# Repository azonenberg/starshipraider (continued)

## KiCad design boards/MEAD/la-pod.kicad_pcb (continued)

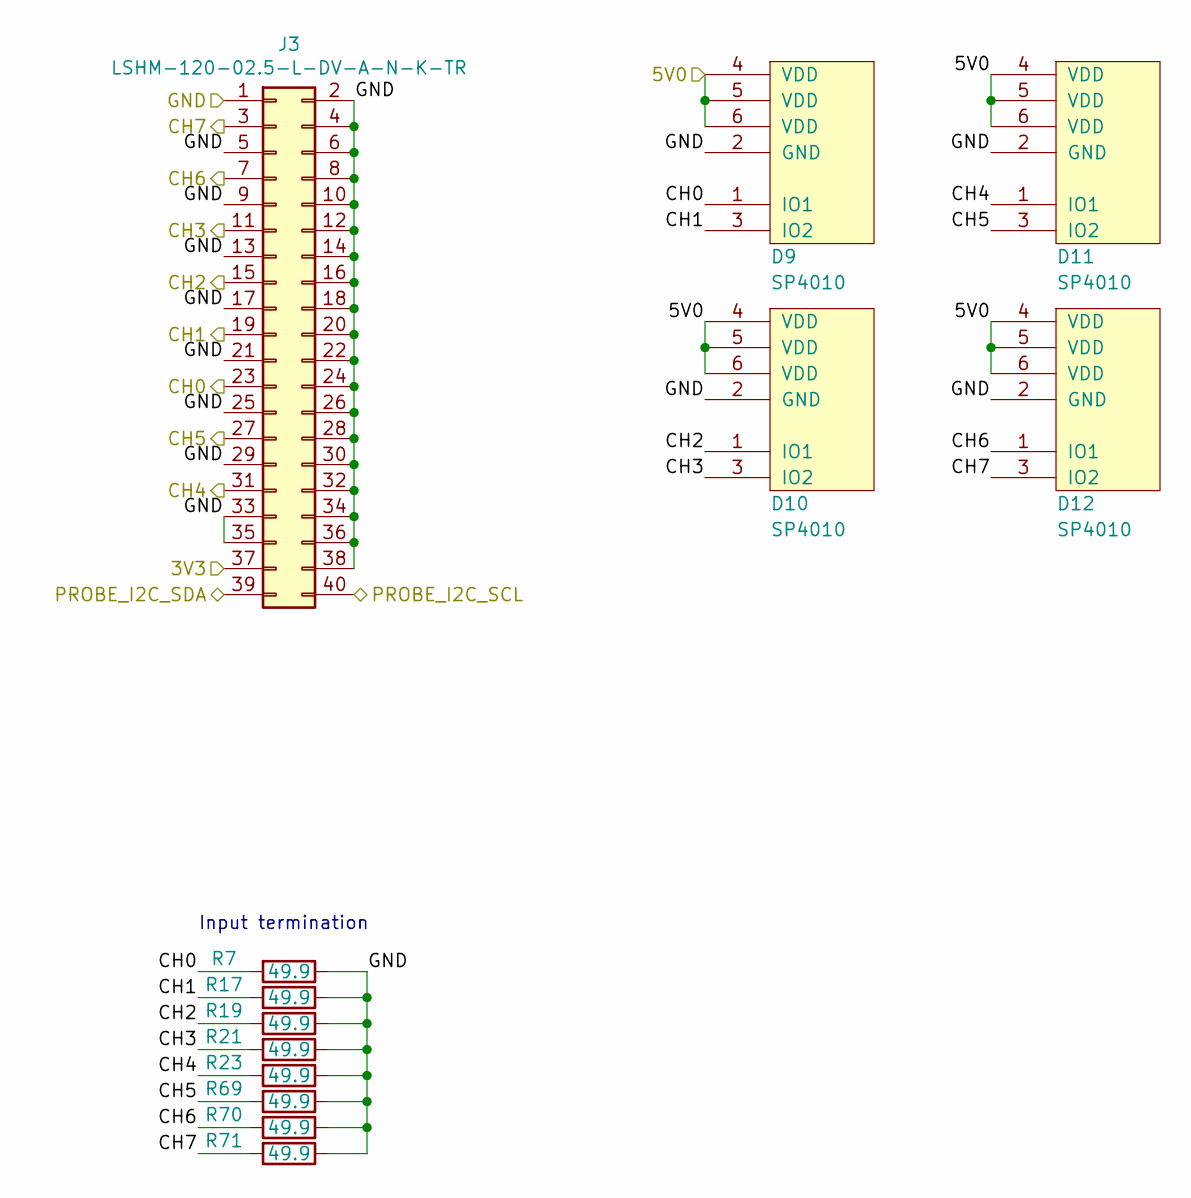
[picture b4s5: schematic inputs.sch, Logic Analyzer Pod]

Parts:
D9, D10, D11, D12: SP4010; SOT23_6
J3: LSHM-120-02.5-L-DV-A-N-K-TR; CONN_SAMTEC_LSHM-120-02.5-L-DV-A-N-K-TR
R7, R17, R19, R21, R23, R69, R70, R71: 49.9; EIA_0402_RES_NOSILK

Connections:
/3V3: J3.37; also elsewhere on the board
/5V0: D9.4 (VDD), D9.5 (VDD), D9.6 (VDD), D10.4 (VDD), D10.5 (VDD), D10.6 (VDD), D11.4 (VDD), D11.5 (VDD), D11.6 (VDD), D12.4 (VDD), D12.5 (VDD), D12.6 (VDD); also elsewhere on the board
/Comparators/CH0: D9.1 (IO1), J3.23, R7.2; also elsewhere on the board
/Comparators/CH1: D9.3 (IO2), J3.19, R17.2; also elsewhere on the board
/Comparators/CH2: D10.1 (IO1), J3.15, R19.2; also elsewhere on the board
/Comparators/CH3: D10.3 (IO2), J3.11, R21.2; also elsewhere on the board
/Comparators/CH4: D11.1 (IO1), J3.31, R23.2; also elsewhere on the board
/Comparators/CH5: D11.3 (IO2), J3.27, R69.2; also elsewhere on the board
/Comparators/CH6: D12.1 (IO1), J3.7, R70.2; also elsewhere on the board
/Comparators/CH7: D12.3 (IO2), J3.3, R71.2; also elsewhere on the board
/GND: D9.2 (GND), D10.2 (GND), D11.2 (GND), D12.2 (GND), J3.1, J3.2, J3.4, J3.5, J3.6, J3.8, J3.9, J3.10, J3.12, J3.13, J3.14, J3.16, J3.17, J3.18, J3.20, J3.21, J3.22, J3.24, J3.25, J3.26, J3.28, J3.29, J3.30, J3.32, J3.33, J3.34, J3.35, J3.36, J3.38, R7.1, R17.1, R19.1, R21.1, R23.1, R69.1, R70.1, R71.1; also elsewhere on the board
/PROBE_I2C_SCL: J3.40; also elsewhere on the board
/PROBE_I2C_SDA: J3.39; also elsewhere on the board

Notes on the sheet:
Input termination

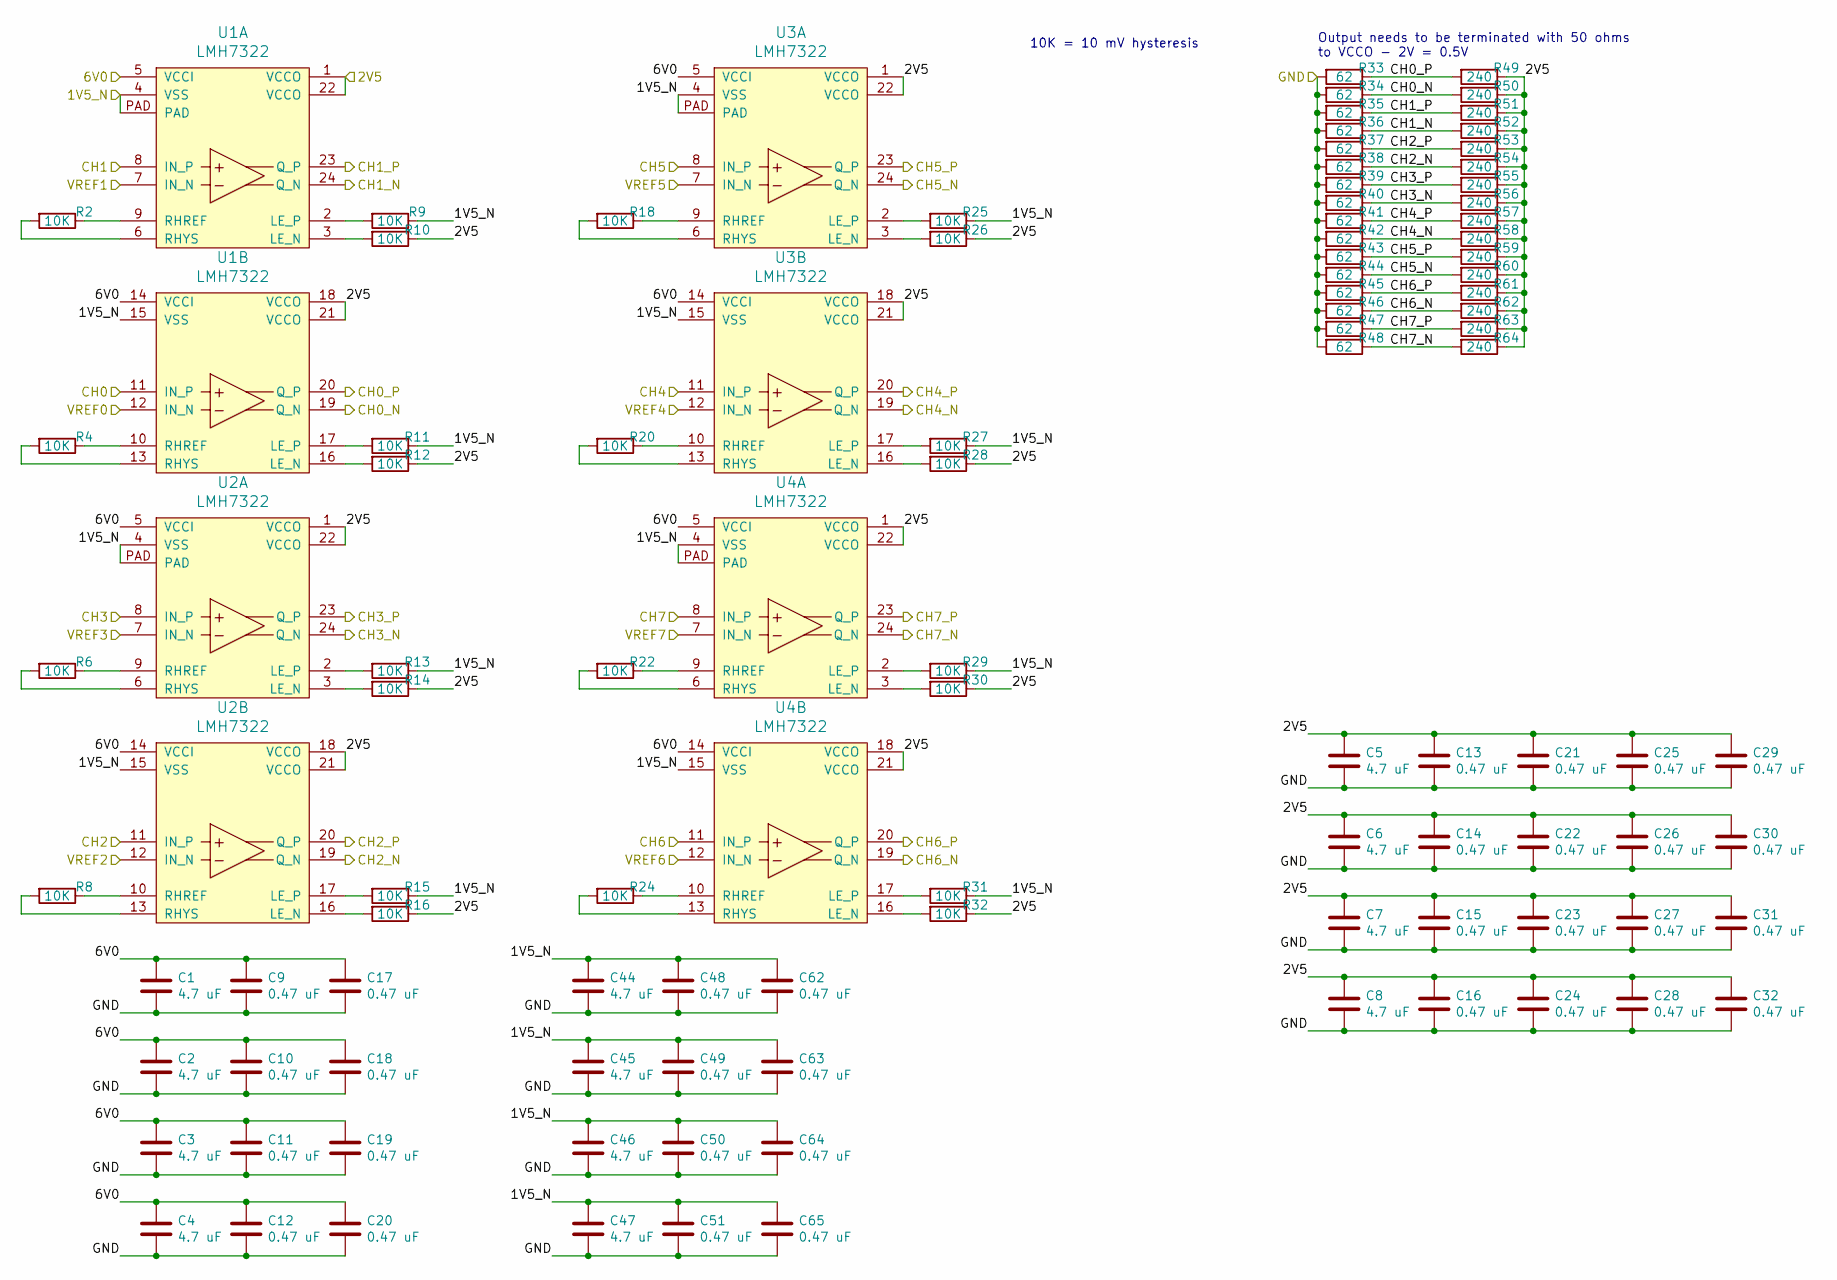
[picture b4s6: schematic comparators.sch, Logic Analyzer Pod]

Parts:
C1, C2, C3, C4, C5, C6, C7, C8, C44, C45, C46, C47: 4.7 uF; EIA_0603_CAP_NOSILK
C9, C10, C11, C12, C13, C14, C15, C16, C17, C18, C19, C20, C21, C22, C23, C24, C25, C26, C27, C28, C29, C30, C31, C32, C48, C49, C50, C51, C62, C63, C64, C65: 0.47 uF; EIA_0402_CAP_NOSILK
R2, R4, R6, R8, R9, R10, R11, R12, R13, R14, R15, R16, R18, R20, R22, R24, R25, R26, R27, R28, R29, R30, R31, R32: 10K; EIA_0402_RES_NOSILK
R33, R34, R35, R36, R37, R38, R39, R40, R41, R42, R43, R44, R45, R46, R47, R48: 62; EIA_0402_RES_NOSILK
R49, R50, R51, R52, R53, R54, R55, R56, R57, R58, R59, R60, R61, R62, R63, R64: 240; EIA_0402_RES_NOSILK
U1, U2, U3, U4: LMH7322; QFN_24_0.5MM_4x4MM

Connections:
/1V5_N: C44.1, C45.1, C46.1, C47.1, C48.1, C49.1, C50.1, C51.1, C62.1, C63.1, C64.1, C65.1, R9.1, R11.1, R13.1, R15.1, R25.1, R27.1, R29.1, R31.1, U1.4 (VSS), U1.15 (VSS), U1.PAD, U2.4 (VSS), U2.15 (VSS), U2.PAD, U3.4 (VSS), U3.15 (VSS), U3.PAD, U4.4 (VSS), U4.15 (VSS), U4.PAD; also elsewhere on the board
/2V5: C5.1, C6.1, C7.1, C8.1, C13.1, C14.1, C15.1, C16.1, C21.1, C22.1, C23.1, C24.1, C25.1, C26.1, C27.1, C28.1, C29.1, C30.1, C31.1, C32.1, R10.1, R12.1, R14.1, R16.1, R26.1, R28.1, R30.1, R32.1, R49.1, R50.1, R51.1, R52.1, R53.1, R54.1, R55.1, R56.1, R57.1, R58.1, R59.1, R60.1, R61.1, R62.1, R63.1, R64.1, U1.1 (VCCO), U1.18 (VCCO), U1.21 (VCCO), U1.22 (VCCO), U2.1 (VCCO), U2.18 (VCCO), U2.21 (VCCO), U2.22 (VCCO), U3.1 (VCCO), U3.18 (VCCO), U3.21 (VCCO), U3.22 (VCCO), U4.1 (VCCO), U4.18 (VCCO), U4.21 (VCCO), U4.22 (VCCO); also elsewhere on the board
/6V0: C1.1, C2.1, C3.1, C4.1, C9.1, C10.1, C11.1, C12.1, C17.1, C18.1, C19.1, C20.1, U1.5 (VCCI), U1.14 (VCCI), U2.5 (VCCI), U2.14 (VCCI), U3.5 (VCCI), U3.14 (VCCI), U4.5 (VCCI), U4.14 (VCCI); also elsewhere on the board
/Comparators/CH0: U1.11 (IN_P); also elsewhere on the board
/Comparators/CH1: U1.8 (IN_P); also elsewhere on the board
/Comparators/CH2: U2.11 (IN_P); also elsewhere on the board
/Comparators/CH3: U2.8 (IN_P); also elsewhere on the board
/Comparators/CH4: U3.11 (IN_P); also elsewhere on the board
/Comparators/CH5: U3.8 (IN_P); also elsewhere on the board
/Comparators/CH6: U4.11 (IN_P); also elsewhere on the board
/Comparators/CH7: U4.8 (IN_P); also elsewhere on the board
/Comparators/VREF1: U1.7 (IN_N); also elsewhere on the board
/Comparators/VREF2: U2.12 (IN_N); also elsewhere on the board
/Comparators/VREF3: U2.7 (IN_N); also elsewhere on the board
/Comparators/VREF4: U3.12 (IN_N); also elsewhere on the board
/Comparators/VREF5: U3.7 (IN_N); also elsewhere on the board
/Comparators/VREF6: U4.12 (IN_N); also elsewhere on the board
/Comparators/VREF7: U4.7 (IN_N); also elsewhere on the board
/GND: C1.2, C2.2, C3.2, C4.2, C5.2, C6.2, C7.2, C8.2, C9.2, C10.2, C11.2, C12.2, C13.2, C14.2, C15.2, C16.2, C17.2, C18.2, C19.2, C20.2, C21.2, C22.2, C23.2, C24.2, C25.2, C26.2, C27.2, C28.2, C29.2, C30.2, C31.2, C32.2, C44.2, C45.2, C46.2, C47.2, C48.2, C49.2, C50.2, C51.2, C62.2, C63.2, C64.2, C65.2, R33.2, R34.2, R35.2, R36.2, R37.2, R38.2, R39.2, R40.2, R41.2, R42.2, R43.2, R44.2, R45.2, R46.2, R47.2, R48.2; also elsewhere on the board
/TX0_N: R34.1, R50.2, U1.19 (Q_N); also elsewhere on the board
/TX0_P: R33.1, R49.2, U1.20 (Q_P); also elsewhere on the board
/TX1_N: R36.1, R52.2, U1.24 (Q_N); also elsewhere on the board
/TX1_P: R35.1, R51.2, U1.23 (Q_P); also elsewhere on the board
/TX2_N: R38.1, R54.2, U2.19 (Q_N); also elsewhere on the board
/TX2_P: R37.1, R53.2, U2.20 (Q_P); also elsewhere on the board
/TX3_N: R40.1, R56.2, U2.24 (Q_N); also elsewhere on the board
/TX3_P: R39.1, R55.2, U2.23 (Q_P); also elsewhere on the board
/TX4_N: R42.1, R58.2, U3.19 (Q_N); also elsewhere on the board
/TX4_P: R41.1, R57.2, U3.20 (Q_P); also elsewhere on the board
/TX5_N: R44.1, R60.2, U3.24 (Q_N); also elsewhere on the board
/TX5_P: R43.1, R59.2, U3.23 (Q_P); also elsewhere on the board
/TX6_N: R46.1, R62.2, U4.19 (Q_N); also elsewhere on the board
/TX6_P: R45.1, R61.2, U4.20 (Q_P); also elsewhere on the board
/TX7_N: R48.1, R64.2, U4.24 (Q_N); also elsewhere on the board
/TX7_P: R47.1, R63.2, U4.23 (Q_P); also elsewhere on the board
/VREF0: U1.12 (IN_N); also elsewhere on the board
unnamed: R2.1, U1.9 (RHREF)
unnamed: R2.2, U1.6 (RHYS)
unnamed: R4.1, U1.10 (RHREF)
unnamed: R4.2, U1.13 (RHYS)
unnamed: R6.1, U2.9 (RHREF)
unnamed: R6.2, U2.6 (RHYS)
unnamed: R8.1, U2.10 (RHREF)
unnamed: R8.2, U2.13 (RHYS)
unnamed: R9.2, U1.2 (LE_P)
unnamed: R10.2, U1.3 (LE_N)
unnamed: R11.2, U1.17 (LE_P)
unnamed: R12.2, U1.16 (LE_N)
unnamed: R13.2, U2.2 (LE_P)
unnamed: R14.2, U2.3 (LE_N)
unnamed: R15.2, U2.17 (LE_P)
unnamed: R16.2, U2.16 (LE_N)
unnamed: R18.1, U3.9 (RHREF)
unnamed: R18.2, U3.6 (RHYS)
unnamed: R20.1, U3.10 (RHREF)
unnamed: R20.2, U3.13 (RHYS)
unnamed: R22.1, U4.9 (RHREF)
unnamed: R22.2, U4.6 (RHYS)
unnamed: R24.1, U4.10 (RHREF)
unnamed: R24.2, U4.13 (RHYS)
unnamed: R25.2, U3.2 (LE_P)
unnamed: R26.2, U3.3 (LE_N)
unnamed: R27.2, U3.17 (LE_P)
unnamed: R28.2, U3.16 (LE_N)
unnamed: R29.2, U4.2 (LE_P)
unnamed: R30.2, U4.3 (LE_N)
unnamed: R31.2, U4.17 (LE_P)
unnamed: R32.2, U4.16 (LE_N)

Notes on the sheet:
Output needs to be terminated with 50 ohms to VCCO - 2V = 0.5V
10K = 10 mV hysteresis

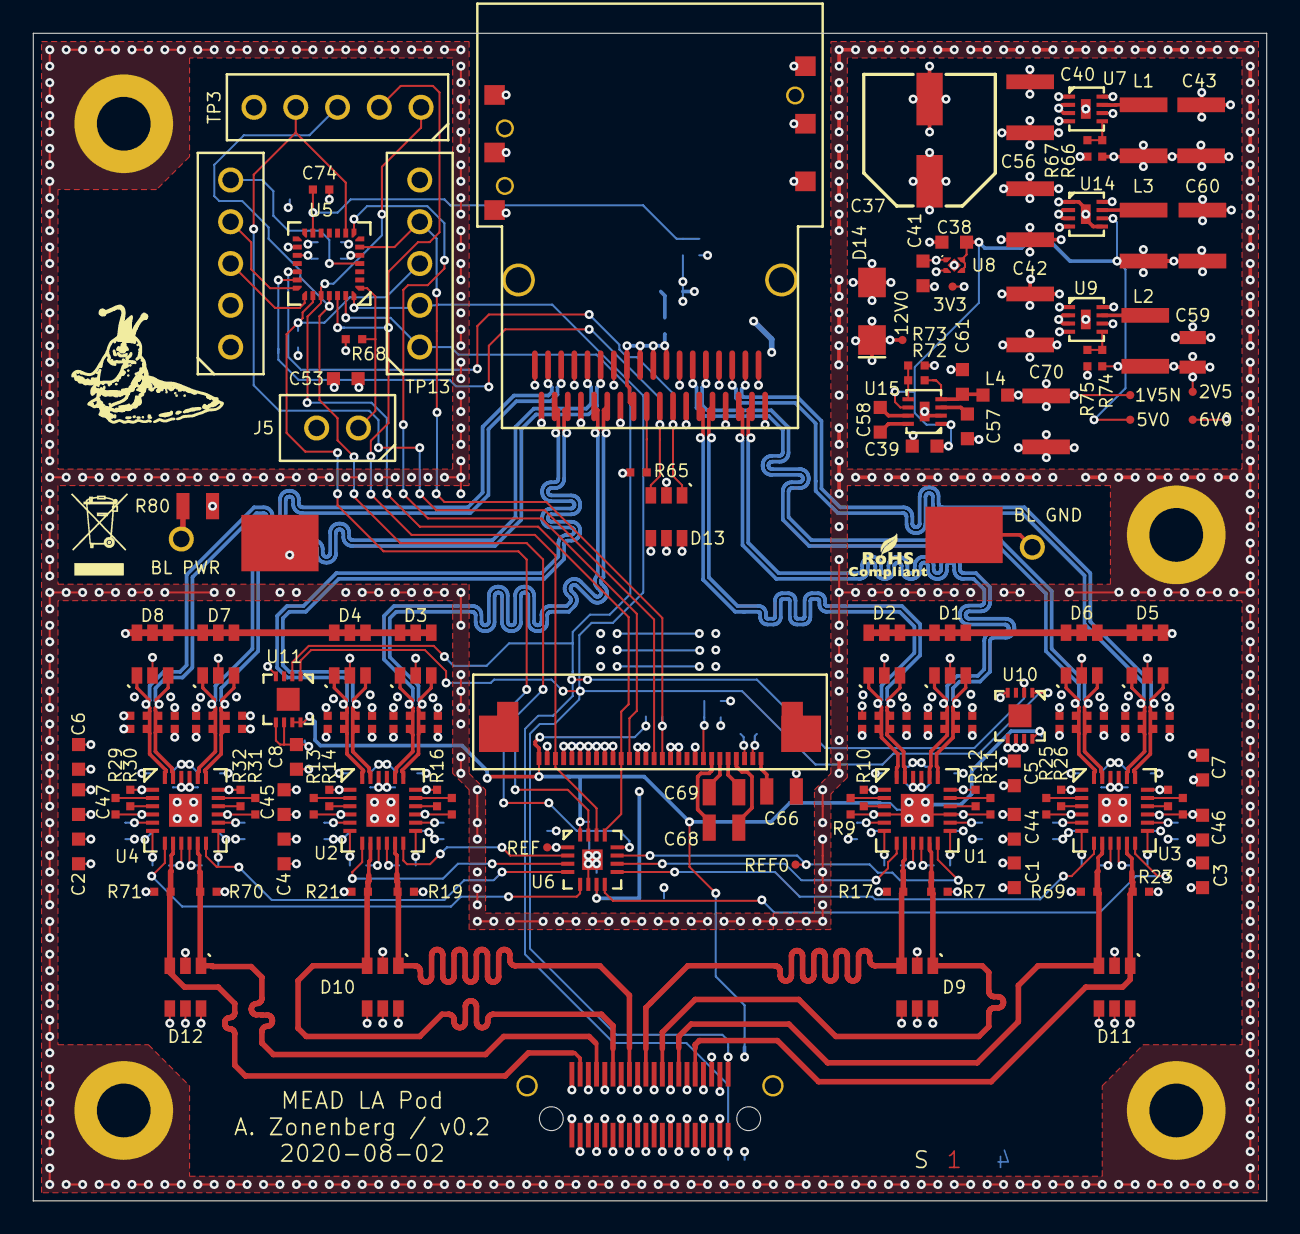
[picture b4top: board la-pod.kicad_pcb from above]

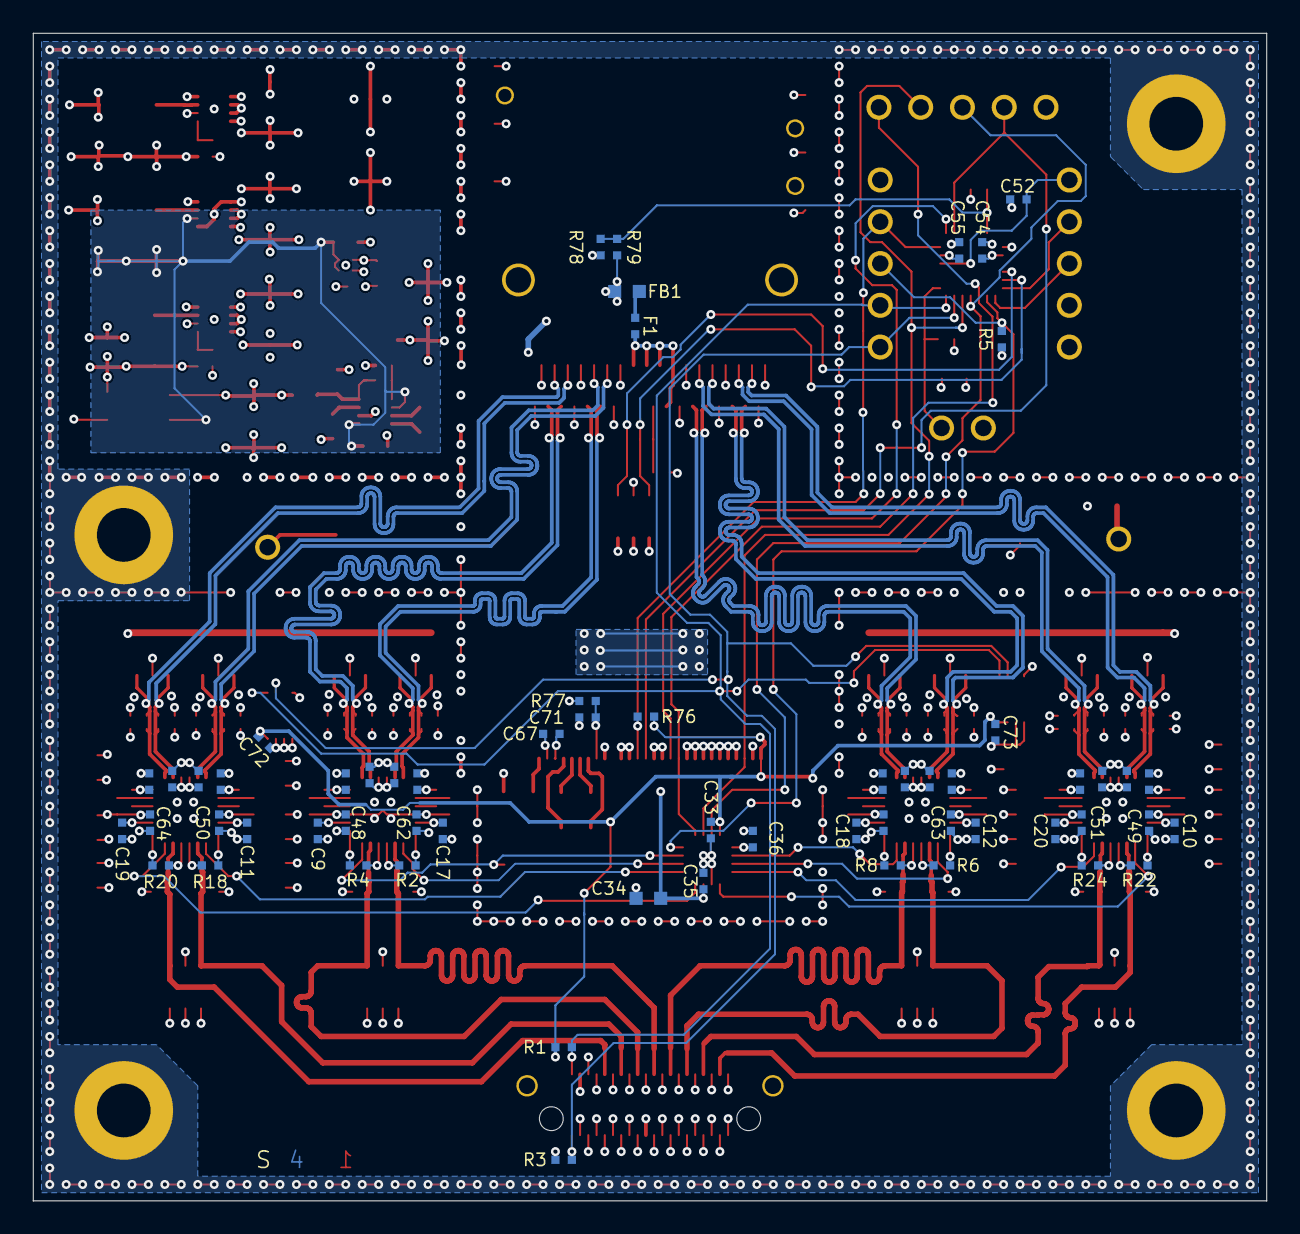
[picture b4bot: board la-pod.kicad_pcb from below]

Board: 4 copper layers, 75.0 x 71.0 mm, 210 parts (60 on the bottom side), 110 nets.

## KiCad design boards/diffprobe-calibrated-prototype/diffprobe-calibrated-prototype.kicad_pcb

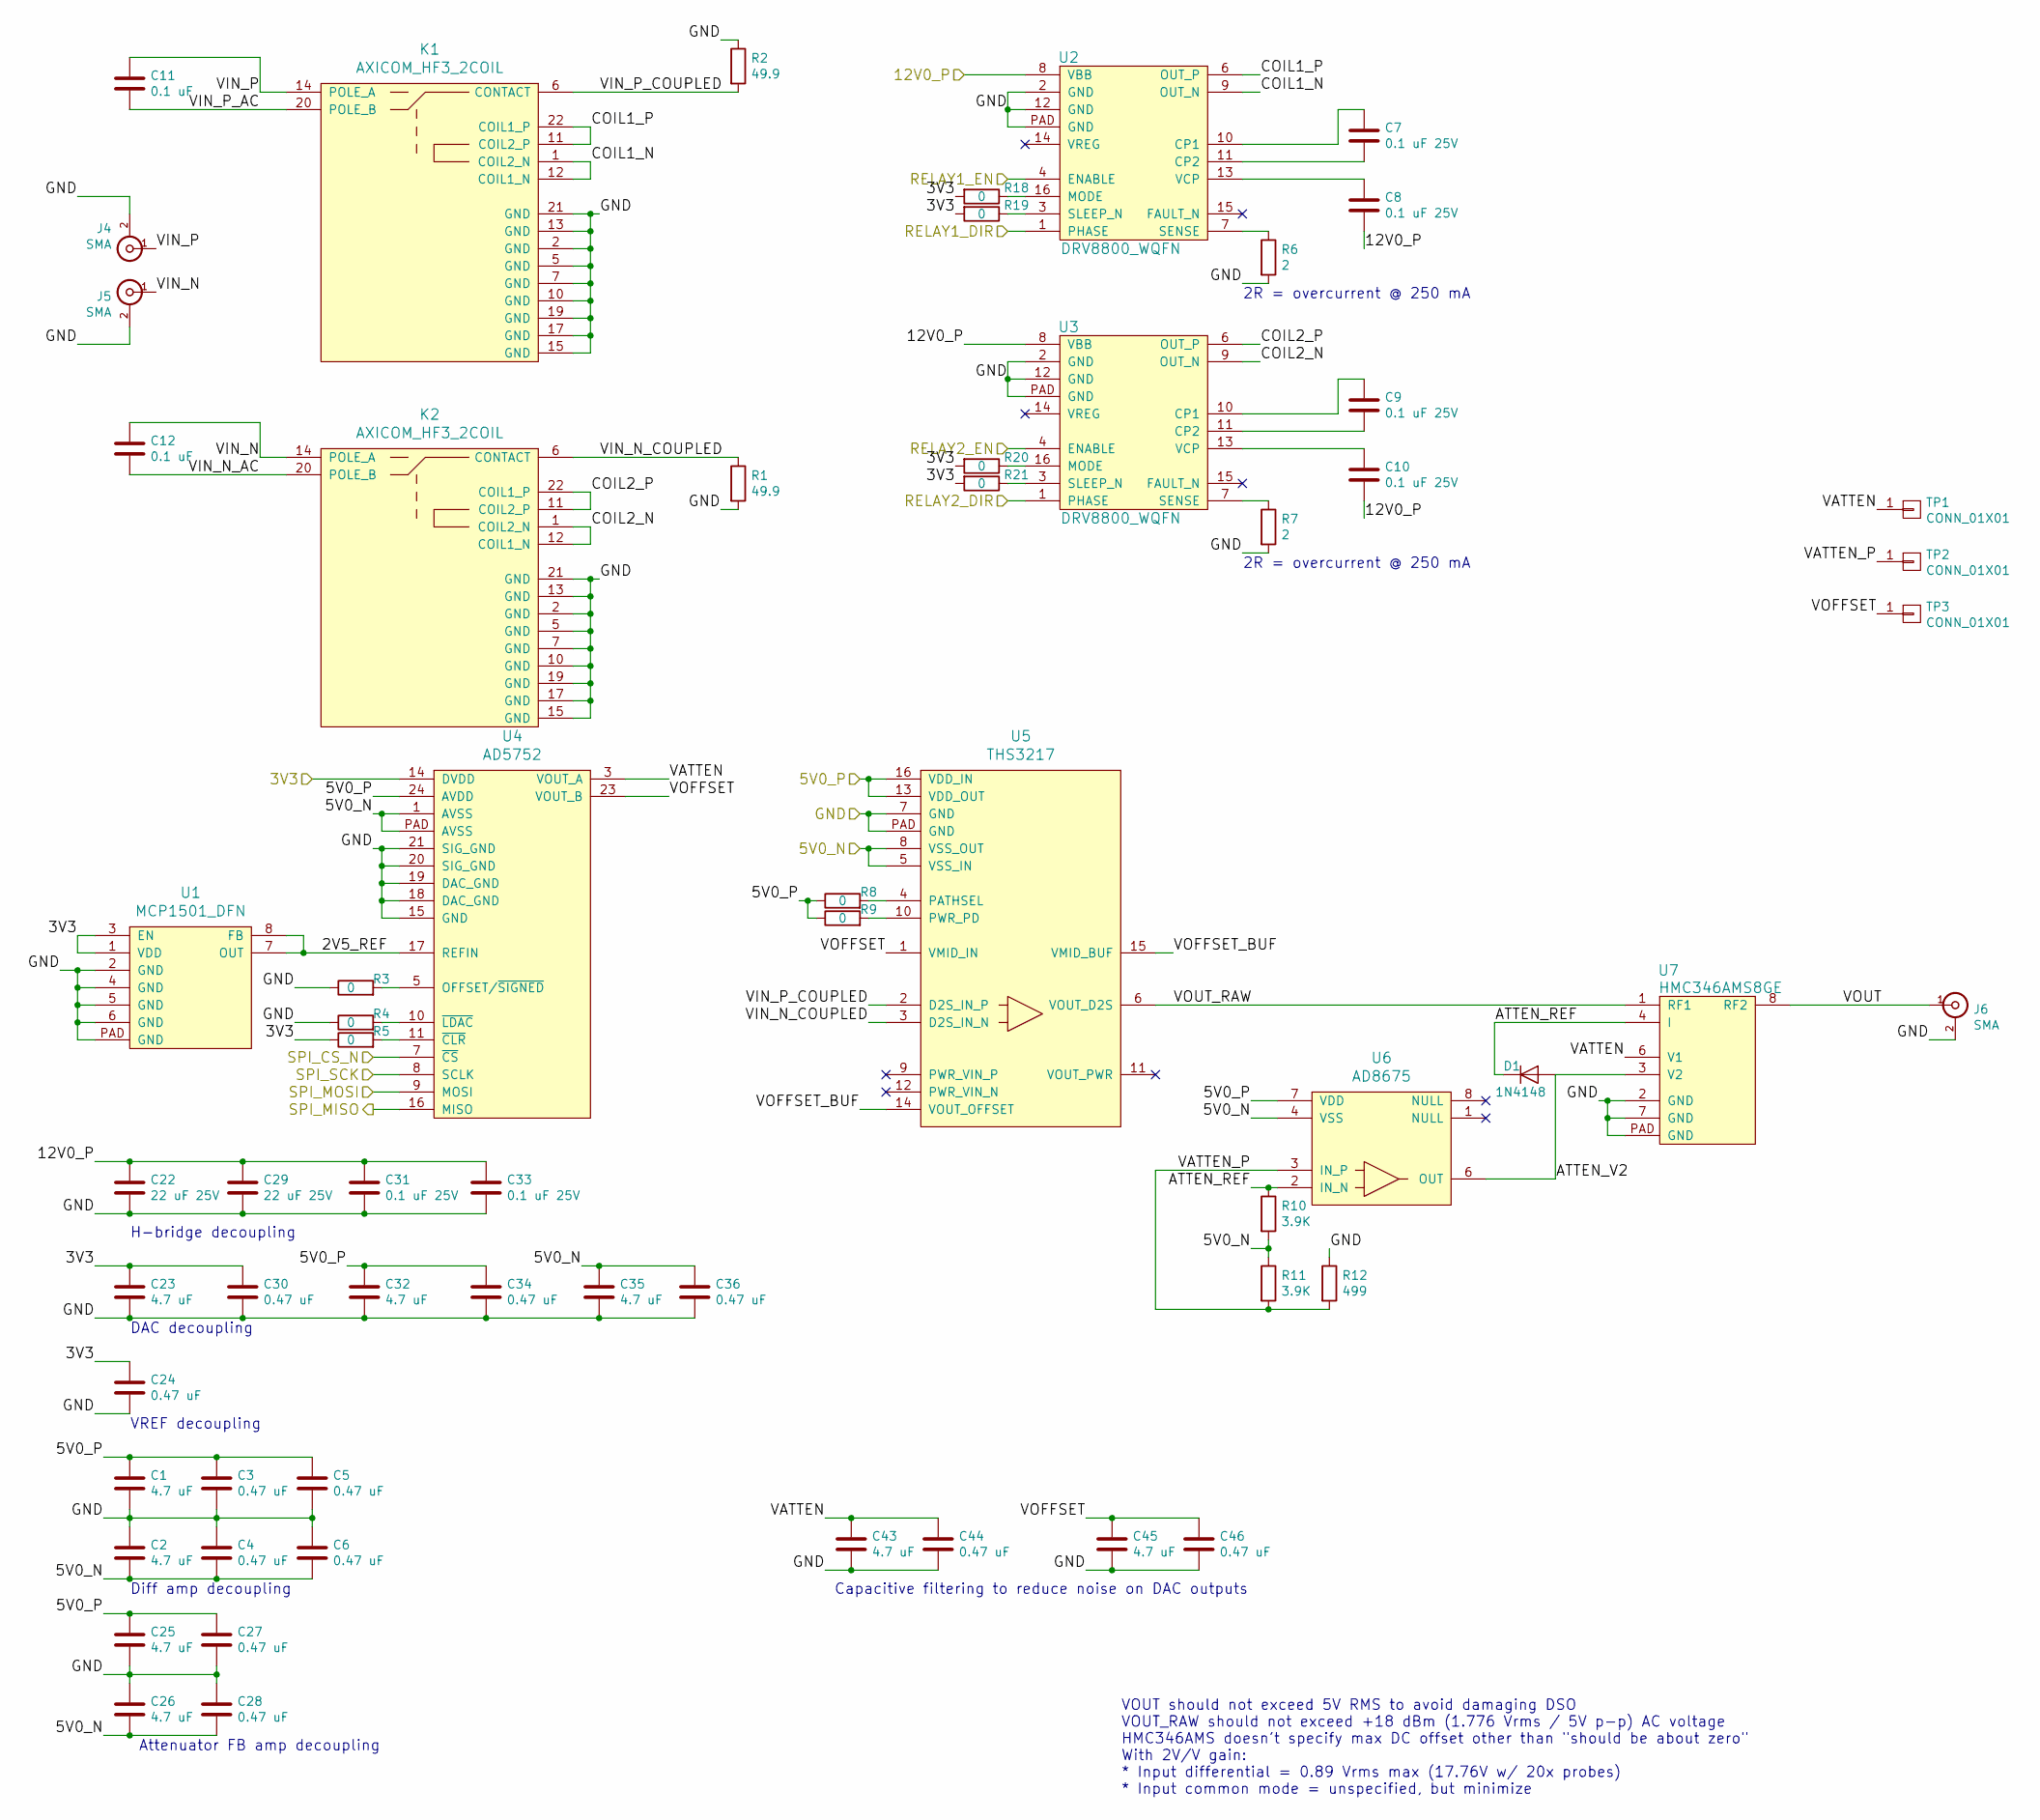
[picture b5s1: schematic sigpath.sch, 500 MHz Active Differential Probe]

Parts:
C1, C2, C23, C25, C26, C32, C35, C43, C45: 4.7 uF; EIA_0603_CAP_NOSILK
C3, C4, C5, C6, C24, C27, C28, C30, C34, C36, C44, C46: 0.47 uF; EIA_0402_CAP_NOSILK
C7, C8, C9, C10, C31, C33: 0.1 uF 25V; EIA_0402_CAP_NOSILK
C11, C12: 0.1 uF; EIA_0402_CAP_NOSILK
C22, C29: 22 uF 25V; EIA_1812_CAP_NOSILK
D1: 1N4148; SOD123
J4, J5, J6: SMA; CONN_SMA_EDGE_SAMTEC_SMA_J_P_H_ST_EM1
K1, K2: AXICOM_HF3_2COIL; RELAY_TE_HF3_2COIL_50OHM
R1, R2: 49.9; EIA_0402_RES_NOSILK
R3, R4, R5, R8, R9, R18, R19, R20, R21: 0; EIA_0402_RES_NOSILK
R6, R7: 2; EIA_0402_RES_NOSILK
R10, R11: 3.9K; EIA_0402_RES_NOSILK
R12: 499; EIA_0402_RES_NOSILK
TP1, TP2, TP3: CONN_01X01; TESTPOINT_SMT_0.5MM
U1: MCP1501_DFN; DFN_8_0.5MM_2x2MM
U2, U3: DRV8800_WQFN; QFN_16_0.65MM_4x4MM
U4: AD5752; TSSOP_24_0.65MM_5MM_EPAD_5x3p2
U5: THS3217; QFN_16_0.65MM_4x4MM
U6: AD8675; SOP_8_0.5MM_3MM
U7: HMC346AMS8GE; SOP_8_0.5MM_3MM_EPAD

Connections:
/3V3: C23.1, C24.1, C30.1, R5.1, R18.2, R19.2, R20.2, R21.2, U1.1 (VDD), U1.3 (EN), U4.14 (DVDD); also elsewhere on the board
/GND: C1.2, C2.1, C3.2, C4.1, C5.2, C6.1, C22.2, C23.2, C24.2, C25.2, C26.1, C27.2, C28.1, C29.2, C30.2, C31.2, C32.2, C33.2, C34.2, C35.2, C36.2, C43.2, C44.2, C45.2, C46.2, J4.2 (Ext), J5.2 (Ext), J6.2 (Ext), K1.2 (GND), K1.5 (GND), K1.7 (GND), K1.10 (GND), K1.13 (GND), K1.15 (GND), K1.17 (GND), K1.19 (GND), K1.21 (GND), K2.2 (GND), K2.5 (GND), K2.7 (GND), K2.10 (GND), K2.13 (GND), K2.15 (GND), K2.17 (GND), K2.19 (GND), K2.21 (GND), R1.2, R2.1, R3.1, R4.1, R6.2, R7.2, R12.1, U1.2 (GND), U1.4 (GND), U1.5 (GND), U1.6 (GND), U1.PAD (GND), U2.2 (GND), U2.12 (GND), U2.PAD (GND), U3.2 (GND), U3.12 (GND), U3.PAD (GND), U4.15 (GND), U4.18 (DAC_GND), U4.19 (DAC_GND), U4.20 (SIG_GND), U4.21 (SIG_GND), U5.7 (GND), U5.PAD (GND), U7.2 (GND), U7.7 (GND), U7.PAD (GND); also elsewhere on the board
/Microcontroller/RELAY1_DIR: U2.1 (PHASE); also elsewhere on the board
/Microcontroller/RELAY1_EN: U2.4 (ENABLE); also elsewhere on the board
/Microcontroller/RELAY2_DIR: U3.1 (PHASE); also elsewhere on the board
/Microcontroller/RELAY2_EN: U3.4 (ENABLE); also elsewhere on the board
/Microcontroller/SPI_CS_N: U4.7 (~CS); also elsewhere on the board
/Microcontroller/SPI_MISO: U4.16 (MISO); also elsewhere on the board
/Microcontroller/SPI_MOSI: U4.9 (MOSI); also elsewhere on the board
/Microcontroller/SPI_SCK: U4.8 (SCLK); also elsewhere on the board
/Power Supply/5V0_N: C2.2, C4.2, C6.2, C26.2, C28.2, C35.1, C36.1, R10.2, R11.1, U4.1 (AVSS), U4.PAD (AVSS), U5.5 (VSS_IN), U5.8 (VSS_OUT), U6.4 (VSS); also elsewhere on the board
/Power Supply/5V0_P: C1.1, C3.1, C5.1, C25.1, C27.1, C32.1, C34.1, R8.1, R9.1, U4.24 (AVDD), U5.13 (VDD_OUT), U5.16 (VDD_IN), U6.7 (VDD); also elsewhere on the board
/Power Supply/12V0_P: C8.2, C10.2, C22.1, C29.1, C31.1, C33.1, U2.8 (VBB), U3.8 (VBB); also elsewhere on the board
/Signal Path/2V5_REF: U1.7 (OUT), U1.8 (FB), U4.17 (REFIN)
/Signal Path/ATTEN_REF: D1.1 (K), R10.1, U6.2 (IN_N), U7.4 (I)
/Signal Path/ATTEN_V2: D1.2 (A), U6.6 (OUT), U7.3 (V2)
/Signal Path/COIL1_N: K1.1 (COIL2_N), K1.12 (COIL1_N), U2.9 (OUT_N)
/Signal Path/COIL1_P: K1.11 (COIL2_P), K1.22 (COIL1_P), U2.6 (OUT_P)
/Signal Path/COIL2_N: K2.1 (COIL2_N), K2.12 (COIL1_N), U3.9 (OUT_N)
/Signal Path/COIL2_P: K2.11 (COIL2_P), K2.22 (COIL1_P), U3.6 (OUT_P)
/Signal Path/VATTEN: C43.1, C44.1, TP1.1, U4.3 (VOUT_A), U7.6 (V1)
/Signal Path/VATTEN_P: R11.2, R12.2, TP2.1, U6.3 (IN_P)
/Signal Path/VIN_N: C12.1, J5.1 (In), K2.14 (POLE_A)
/Signal Path/VIN_N_AC: C12.2, K2.20 (POLE_B)
/Signal Path/VIN_N_COUPLED: K2.6 (CONTACT), R1.1, U5.3 (D2S_IN_N)
/Signal Path/VIN_P: C11.1, J4.1 (In), K1.14 (POLE_A)
/Signal Path/VIN_P_AC: C11.2, K1.20 (POLE_B)
/Signal Path/VIN_P_COUPLED: K1.6 (CONTACT), R2.2, U5.2 (D2S_IN_P)
/Signal Path/VOFFSET: C45.1, C46.1, TP3.1, U4.23 (VOUT_B), U5.1 (VMID_IN)
/Signal Path/VOFFSET_BUF: U5.14 (VOUT_OFFSET), U5.15 (VMID_BUF)
/Signal Path/VOUT: J6.1 (In), U7.8 (RF2)
/Signal Path/VOUT_RAW: U5.6 (VOUT_D2S), U7.1 (RF1)
unnamed: C7.1, U2.10 (CP1)
unnamed: C7.2, U2.11 (CP2)
unnamed: C8.1, U2.13 (VCP)
unnamed: C9.1, U3.10 (CP1)
unnamed: C9.2, U3.11 (CP2)
unnamed: C10.1, U3.13 (VCP)
unnamed: R3.2, U4.5 (OFFSET/~SIGNED)
unnamed: R4.2, U4.10 (~LDAC)
unnamed: R5.2, U4.11 (~CLR)
unnamed: R6.1, U2.7 (SENSE)
unnamed: R7.1, U3.7 (SENSE)
unnamed: R8.2, U5.4 (PATHSEL)
unnamed: R9.2, U5.10 (PWR_PD)
unnamed: R18.1, U2.16 (MODE)
unnamed: R19.1, U2.3 (SLEEP_N)
unnamed: R20.1, U3.16 (MODE)
unnamed: R21.1, U3.3 (SLEEP_N)

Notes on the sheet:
VOUT should not exceed 5V RMS to avoid damaging DSO VOUT_RAW should not exceed +18 dBm (1.776 Vrms / 5V p-p) AC voltage HMC346AMS doesn't specify max DC offset other than "should be about zero" With 2V/V gain: * Input differential = 0.89 Vrms max (17.76V w/ 20x probes) * Input common mode = unspeci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
2R = overcurrent @ 250 mA
H-bridge decoupling
Diff amp decoupling
DAC decoupling
VREF decoupling
Attenuator FB amp decoupling
Capacitive filtering to reduce noise on DAC outputs

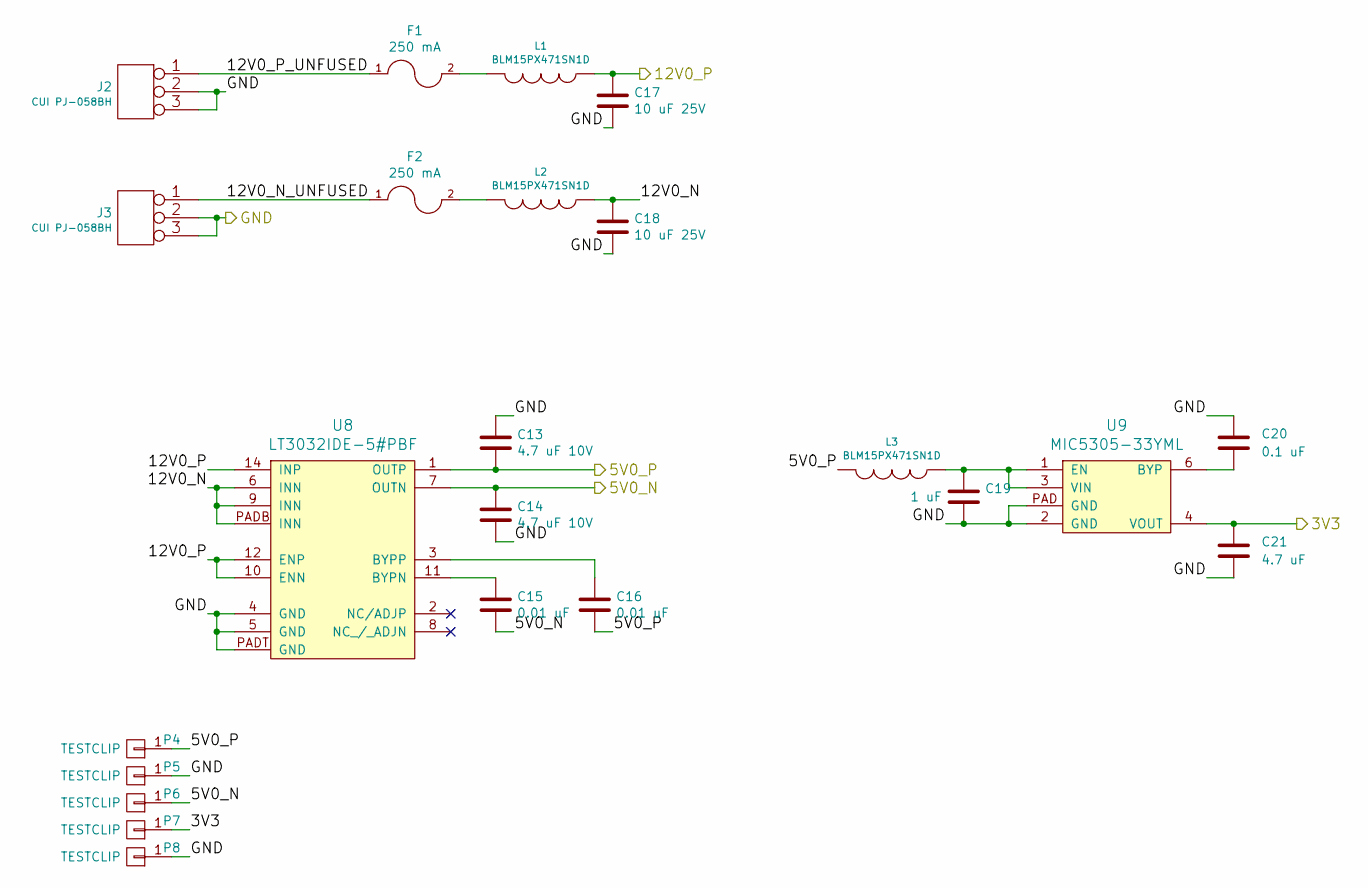
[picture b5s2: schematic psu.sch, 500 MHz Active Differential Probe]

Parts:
C13, C14: 4.7 uF 10V; EIA_0603_CAP_NOSILK
C15, C16: 0.01 uF; EIA_0402_CAP_NOSILK
C17, C18: 10 uF 25V; EIA_1210_CAP_NOSILK
C19: 1 uF; EIA_0402_CAP_NOSILK
C20: 0.1 uF; EIA_0402_CAP_NOSILK
C21: 4.7 uF; EIA_0603_CAP_NOSILK
F1, F2: 250 mA; EIA_0402_RES_NOSILK
J2, J3: CUI PJ-058BH; CONN_CUI_PJ-058BH_HIPWR_BARREL_NOSLOT
L1, L2, L3: BLM15PX471SN1D; EIA_0402_RES_NOSILK
P4, P5, P6, P7, P8: TESTCLIP; TESTPOINT_SMT_KEYSTONE_5016
U8: LT3032IDE-5#PBF; DFN_14_0.5MM_4x3MM_DUALPAD_LTC_DE14MA
U9: MIC5305-33YML; DFN_6_0.65MM_2x2MM

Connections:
/3V3: C21.1, P7.1, U9.4 (VOUT); also elsewhere on the board
/GND: C13.1, C14.2, C17.2, C18.2, C19.2, C20.1, C21.2, J2.2 (PM), J2.3, J3.2 (PM), J3.3, P5.1, P8.1, U8.4 (GND), U8.5 (GND), U8.PADT (GND), U9.2 (GND), U9.PAD (GND); also elsewhere on the board
/Power Supply/5V0_N: C14.1, C15.2, P6.1, U8.7 (OUTN); also elsewhere on the board
/Power Supply/5V0_P: C13.2, C16.2, L3.2, P4.1, U8.1 (OUTP); also elsewhere on the board
/Power Supply/12V0_N: C18.1, L2.1, U8.6 (INN), U8.9 (INN), U8.PADB (INN)
/Power Supply/12V0_N_UNFUSED: F2.1, J3.1
/Power Supply/12V0_P: C17.1, L1.1, U8.10 (ENN), U8.12 (ENP), U8.14 (INP); also elsewhere on the board
/Power Supply/12V0_P_UNFUSED: F1.1, J2.1
unnamed: C15.1, U8.11 (BYPN)
unnamed: C16.1, U8.3 (BYPP)
unnamed: C19.1, L3.1, U9.1 (EN), U9.3 (VIN)
unnamed: C20.2, U9.6 (BYP)
unnamed: F1.2, L1.2
unnamed: F2.2, L2.2
